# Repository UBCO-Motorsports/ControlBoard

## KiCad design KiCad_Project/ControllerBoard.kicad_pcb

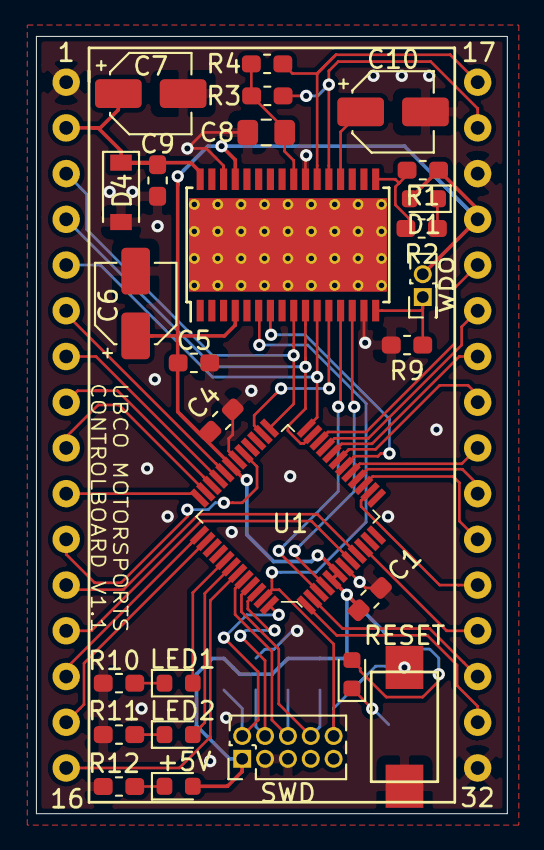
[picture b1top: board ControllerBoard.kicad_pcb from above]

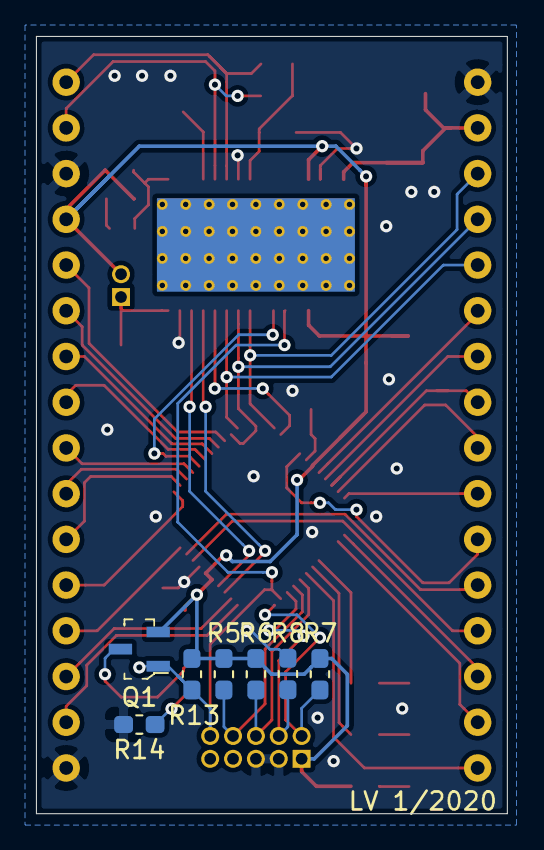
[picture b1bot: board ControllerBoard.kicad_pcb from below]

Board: 2 copper layers, 26.2 x 43.2 mm, 35 parts (7 on the bottom side), 51 nets.

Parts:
C1, C4, C5, C9: 100n; C_0603_1608Metric_Pad1.05x0.95mm_HandSolder
C6, C7, C10: 10u; CP_Elec_4x5.4
C8: 4.7n; C_0805_2012Metric_Pad1.15x1.40mm_HandSolder
D1, D6: LEDR; LED_0603_1608Metric
D2, D3, D5: LEDG; LED_0603_1608Metric
D4: 30v; D_SOD-123
J1: Main Header; Breadboard_Center_32pin
J2: SWD; PinHeader_2x05_P1.27mm_Vertical
J3: WD_Disable; PinHeader_2x01_P1.27mm_Vertical
Q1: BSS84; SOT-23-3
R1, R5, R6, R7, R8, R13: 10k; R_0603_1608Metric_Pad1.05x0.95mm_HandSolder
R2, R10, R11, R12, R14: 220; R_0603_1608Metric_Pad1.05x0.95mm_HandSolder
R3, R4, R9: 1.3k; R_0603_1608Metric_Pad1.05x0.95mm_HandSolder
S1: RESET; PTS636 SK25F SMTR LFS
U1: FS32K116; LQFP-48_7x7mm
U2: UJA1075A; HTSSOP-32-1EP_6.1x11mm_P0.65mm_EP5.2x11mm_Mask4.11x4.36mm_T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

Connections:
+5V: C1.2, C4.1, C5.2, C6.1, D1.2, D5.2, J1.20, J2.1, J3.2, Q1.2, R1.1, R5.1, R6.1, R7.1, R13.1, U1.5, U1.6, U1.31, U2.4, U2.29
+12V: C7.1, C9.2, D4.1, J1.2, U2.32
CANH: J1.18, R3.2, U2.21
CANL: J1.17, R4.2, U2.22
CAN_RX: U1.4, U2.14
CAN_TX: U1.3, U2.13
GND: C1.1, C4.2, C5.1, C6.2, C7.2, C8.2, C9.1, C10.2, D4.2, J1.1, J1.19, J1.32, J2.3, J2.5, R8.2, R9.2, R10.1, R11.1, R12.1, R14.2, S1.2, U1.7, U1.30, U2.15, U2.23, U2.30
I2C_SCL: J1.13, U1.8
I2C_SDA: J1.12, U1.9
LIMP: R1.2, R2.2, U2.17
MISO: J1.4, U1.23, U2.10
MOSI: J1.3, U1.25, U2.9
unnamed: C10.1, U2.20
unnamed: D1.1, R2.1
unnamed: D2.1, R10.2
unnamed: D3.1, R11.2
unnamed: D5.1, R12.2
unnamed: D6.1, R14.1
unnamed: D6.2, Q1.3
PTA0: J1.15, U1.38
PTA1: J1.14, U1.37
PTA2: J1.10, U1.36
PTA3: J1.9, U1.35
PTA7: J1.11, U1.29
PTA11: J1.16, U1.43
PTA12: D3.2, U1.42
PTA13: D2.2, U1.41
PTB4: J1.27, U1.15
PTB5: J1.28, U1.14
PTB13: J1.6, U1.32
PTC1: J1.24, U1.19
PTC2: J1.25, U1.17
PTC3: J1.26, U1.16
PTC14: J1.21, U1.22
PTC15: J1.22, U1.21
PTC16: J1.23, U1.20
PTD0: J1.30, U1.2
PTD1: J1.31, U1.1
PTD2: J1.8, U1.34
PTD3: J1.7, U1.33
PTD16: J1.29, U1.10
RESET: J2.10, Q1.1, R13.2, S1.1, U1.47, U2.6
SBC_INTN: U1.18, U2.7
SCK: J1.5, U1.24, U2.11
SCSN: U1.26, U2.12
SPLIT: C8.1, R3.1, R4.1, U2.24
SWDCLK: J2.4, R8.1, U1.46
SWDIO: J2.2, R7.2, U1.48
SWO: J2.6, R6.2, U1.44
TDI: J2.8, R5.2, U1.45
WD_OFF: J3.1, R9.1, U2.16

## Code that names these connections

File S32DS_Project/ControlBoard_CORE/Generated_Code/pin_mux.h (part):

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**                  Direction                              : <Automatic>
**                  Pin GPIO11                             : <Automatic>
**                  Direction                              : <Automatic>
**                  Pin GPIO12                             : PTA12
**                  Direction                              : Output
**                  Pin GPIO13                             : PTA13
**                  Direction                              : Output
**                Custom name                              : PTB
**                PTB                                      : 
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**                Custom name                              : WDOG
**              Non-peripheral pins                        : 
**            Electrical properties                        : 
**              Pin 1: PTD1                                : 
**                Custom name, Signal name                 : PTD1
**                Interrupt Status Field                   : <Automatic>
**                Interrupt Configuration Field            : <Automatic>
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**                Pull Select Field                        : <Automatic>
**                Initial Value Field                      : <Automatic>
**                Digital Filter Field                     : <Automatic>
**              Pin 2: PTD0                                : 
**                Custom name, Signal name                 : PTD0
**                Interrupt Status Field                   : <Automatic>
**                Interrupt Configuration Field            : <Automatic>
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**                Pull Select Field                        : <Automatic>
**                Initial Value Field                      : <Automatic>
**                Digital Filter Field                     : <Automatic>
**              Pin 10: PTD16                              : 
**                Custom name, Signal name                 : PTD16
**                Interrupt Status Field                   : <Automatic>
**                Interrupt Configuration Field            : <Automatic>
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**                Pull Select Field                        : <Automatic>
**                Initial Value Field                      : <Automatic>
**                Digital Filter Field                     : <Automatic>
**              Pin 14: PTB5                               : 
**                Custom name, Signal name                 : PTB5
**                Interrupt Status Field                   : <Automatic>
**                Interrupt Configuration Field            : <Automatic>
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**                Pull Select Field                        : <Automatic>
**                Initial Value Field                      : <Automatic>
**                Digital Filter Field                     : <Automatic>
**              Pin 15: PTB4                               : 
**                Custom name, Signal name                 : PTB4
**                Interrupt Status Field                   : <Automatic>
**                Interrupt Configuration Field            : <Automatic>
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**                Pull Select Field                        : <Automatic>
**                Initial Value Field                      : <Automatic>
**                Digital Filter Field                     : <Automatic>
**              Pin 16: PTC3                               : 
**                Custom name, Signal name                 : PTC3
**                Interrupt Status Field                   : <Automatic>
**                Interrupt Configuration Field            : <Automatic>
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**                Pull Select Field                        : <Automatic>
**                Initial Value Field                      : <Automatic>
**                Digital Filter Field                     : <Automatic>
**              Pin 17: PTC2                               : 
**                Custom name, Signal name                 : PTC2
**                Interrupt Status Field                   : <Automatic>
**                Interrupt Configuration Field            : <Automatic>
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**                Pull Select Field                        : <Automatic>
**                Initial Value Field                      : <Automatic>
**                Digital Filter Field                     : <Automatic>
**              Pin 19: PTC1                               : 
**                Custom name, Signal name                 : PTC1
**                Interrupt Status Field                   : <Automatic>
**                Interrupt Configuration Field            : <Automatic>
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**                Pull Select Field                        : <Automatic>
**                Initial Value Field                      : <Automatic>
**                Digital Filter Field                     : <Automatic>
**              Pin 20: PTC16                              : 
**                Custom name, Signal name                 : PTC16
**                Interrupt Status Field                   : <Automatic>
**                Interrupt Configuration Field            : <Automatic>
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**                Pull Select Field                        : <Automatic>
**                Initial Value Field                      : <Automatic>
**                Digital Filter Field                     : <Automatic>
**              Pin 21: PTC15                              : 
**                Custom name, Signal name                 : PTC15
**                Interrupt Status Field                   : <Automatic>
**                Interrupt Configuration Field            : <Automatic>
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**                Pull Select Field                        : <Automatic>
**                Initial Value Field                      : <Automatic>
**                Digital Filter Field                     : <Automatic>
**              Pin 22: PTC14                              : 
**                Custom name, Signal name                 : PTC14
**                Interrupt Status Field                   : <Automatic>
**                Interrupt Configuration Field            : <Automatic>
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**                Pull Select Field                        : <Automatic>
**                Initial Value Field                      : <Automatic>
**                Digital Filter Field                     : <Automatic>
**              Pin 29: PTA7                               : 
**                Custom name, Signal name                 : PTA7
**                Interrupt Status Field                   : <Automatic>
**                Interrupt Configuration Field            : <Automatic>
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**                Custom name, Signal name                 : VSS30
**              Pin 31: VDD31                              : 
**                Custom name, Signal name                 : VDD31
**              Pin 32: PTB13                              : 
**                Custom name, Signal name                 : PTB13
**                Interrupt Status Field                   : <Automatic>
**                Interrupt Configuration Field            : <Automatic>
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**                Pull Select Field                        : <Automatic>
**                Initial Value Field                      : <Automatic>
**                Digital Filter Field                     : <Automatic>
**              Pin 33: PTD3                               : 
**                Custom name, Signal name                 : PTD3
**                Interrupt Status Field                   : <Automatic>
**                Interrupt Configuration Field            : <Automatic>
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**                Pull Select Field                        : <Automatic>
**                Initial Value Field                      : <Automatic>
**                Digital Filter Field                     : <Automatic>
**              Pin 34: PTD2                               : 
**                Custom name, Signal name                 : PTD2
**                Interrupt Status Field                   : <Automatic>
**                Interrupt Configuration Field            : <Automatic>
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**                Pull Select Field                        : <Automatic>
**                Initial Value Field                      : <Automatic>
**                Digital Filter Field                     : <Automatic>
**              Pin 35: PTA3                               : 
**                Custom name, Signal name                 : PTA3
**                Interrupt Status Field                   : <Automatic>
**                Interrupt Configuration Field            : <Automatic>
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**                Pull Select Field                        : <Automatic>
**                Initial Value Field                      : <Automatic>
**                Digital Filter Field                     : <Automatic>
**              Pin 36: PTA2                               : 
**                Custom name, Signal name                 : PTA2
**                Interrupt Status Field                   : <Automatic>
**                Interrupt Configuration Field            : <Automatic>
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**                Pull Select Field                        : <Automatic>
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
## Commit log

2019-11-20 Added KiCad Project
2019-11-25 Drove LIMP LED directly from pin instead of from a FET
2019-12-14 Created S32DS Project
2020-01-21 Signifacant work completed on software
2020-01-21 Added a reset LED
2020-01-27 Fixed watchdog problem
    Changed watchdog mode to windowed and adjusted threshold to 128 ms allowing it to be triggered every 100ms by the LPIT timer
2020-01-30 Exported step file
2020-09-21 Readded gitignore

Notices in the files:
S32DS_Project/ControlBoard_CORE/Generated_Code/pin_mux.h:
Copyright 1997 - 2015 Freescale Semiconductor, Inc.
Copyright 2016-2017 NXP
All Rights Reserved.
